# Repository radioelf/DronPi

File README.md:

# DronPi 
Placa sensores para [ardupilot](https://github.com/ArduPilot) y Raspberry o [DuePi](https://github.com/radioelf/Arduino-Due-mod-for-GPIO-compatible-Raspberry-Pi)

Sensores:  
    -***MS5611*** Sensor de presión barométrica (Bus SPI)   
    -***MPU9250*** 	Giroscopio/Acelerómetro/Compás interno/9-AXIS (Bus SPI)   
    -***MCP2515*** CAN Bus (Bus SPI)  
    -***ADS1115*** ADC 16bits (Bus I2C) dirección 0x48, canal 0 tensión, canal 1 intensidad  
    -***PCA9685*** Generador de PWM (Bus I2c) dirección 0x40 y 0x70(ALLCALL)

Periféricos: zumbador, RS-232, i2C, PowerOOF, PPM S-BUS, ADC, Can-Bus, HATs (Hardware Attached on Top)

http://radioelf.blogspot.com.es/  
https://www.youtube.com/watch?v=Fd6dcFx_-Ns (test..)

1/01/17
Changed IC12 SN74LVC1G07 by SN74AHC1G04 (to use S-bus)

## Creative Commons License Disclaimer

UNLESS OTHERWISE MUTUALLY AGREED TO BY THE PARTIES IN WRITING, LICENSOR OFFERS THE WORK AS-IS AND MAKES NO REPRESENTATIONS OR WARRANTIES OF ANY KIND CONCERNING THE WORK, EXPRESS, IMPLIED, STATUTORY OR OTHERWISE, INCLUDING, WITHOUT LIMITATION, WARRANTIES OF TITLE, MERCHANTIBILITY, FITNESS FOR A PARTICULAR PURPOSE, NONINFRINGEMENT, OR THE ABSENCE OF LATENT OR OTHER DEFECTS, ACCURACY, OR THE PRESENCE OF ABSENCE OF ERRORS, WHETHER OR NOT DISCOVERABLE. SOME JURISDICTIONS DO NOT ALLOW THE EXCLUSION OF IMPLIED WARRANTIES, SO SUCH EXCLUSION MAY NOT APPLY TO YOU. EXCEPT TO THE EXTENT REQUIRED BY APPLICABLE LAW, IN NO EVENT WILL LICENSOR BE LIABLE TO YOU ON ANY LEGAL THEORY FOR ANY SPECIAL, INCIDENTAL, CONSEQUENTIAL, PUNITIVE OR EXEMPLARY DAMAGES ARISING OUT OF THIS LICENSE OR THE USE OF THE WORK, EVEN IF LICENSOR HAS BEEN ADVISED OF THE POSSIBILITY OF SUCH DAMAGES.

http://creativecommons.org/licenses/by-sa/3.0/

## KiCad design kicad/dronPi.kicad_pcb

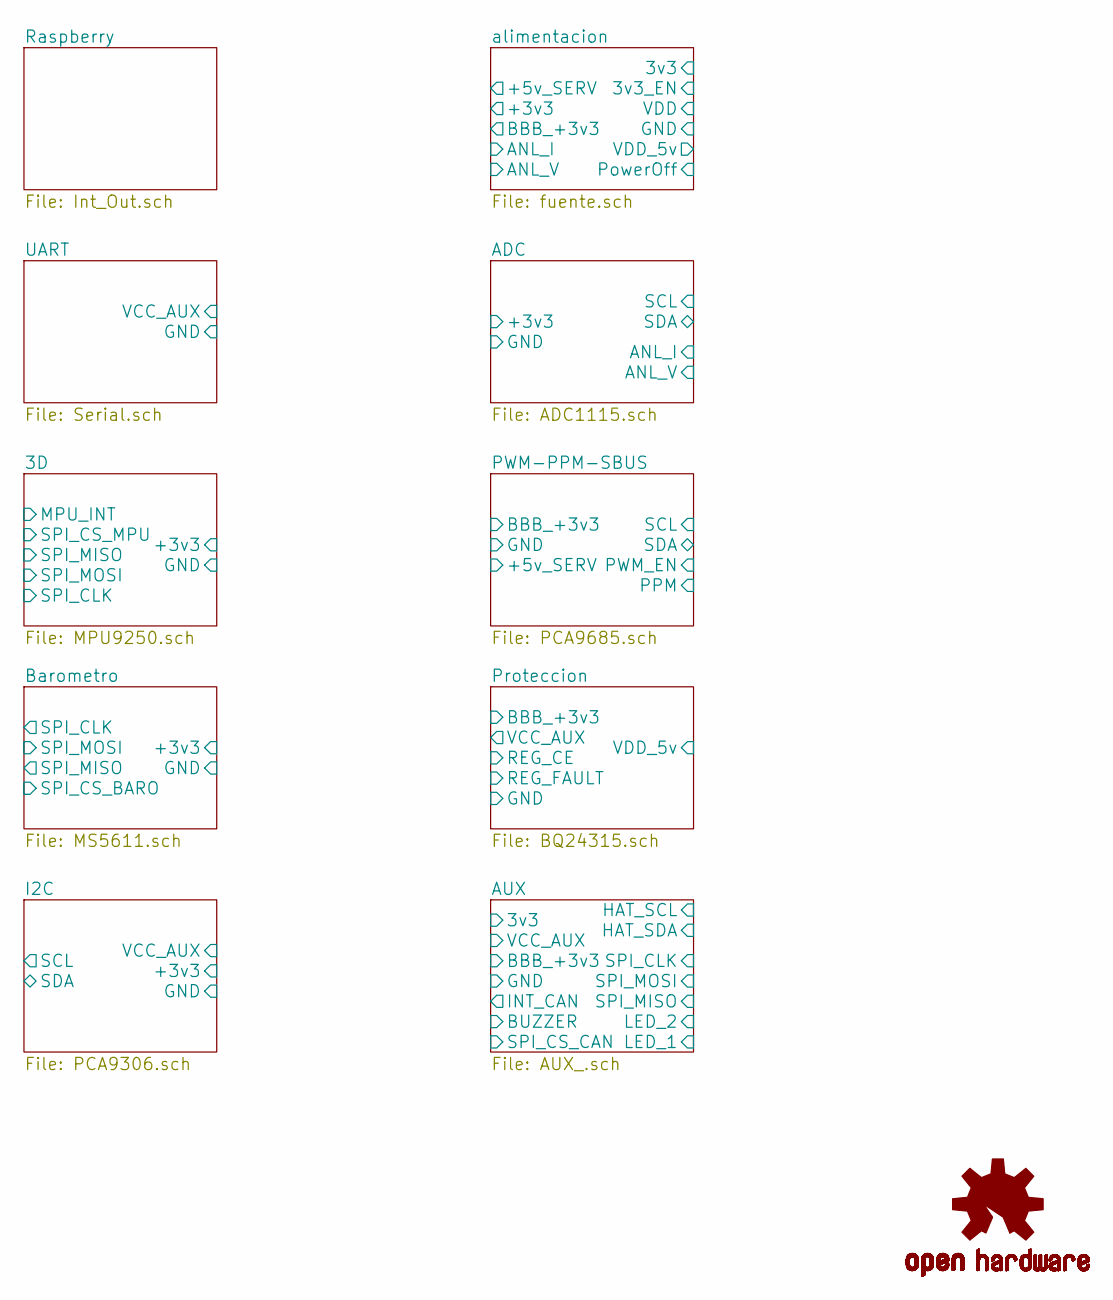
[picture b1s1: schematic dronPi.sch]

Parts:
M1: OSHW-LOGOS; OSHW-Logo2_7.3x6mm_SilkScreen

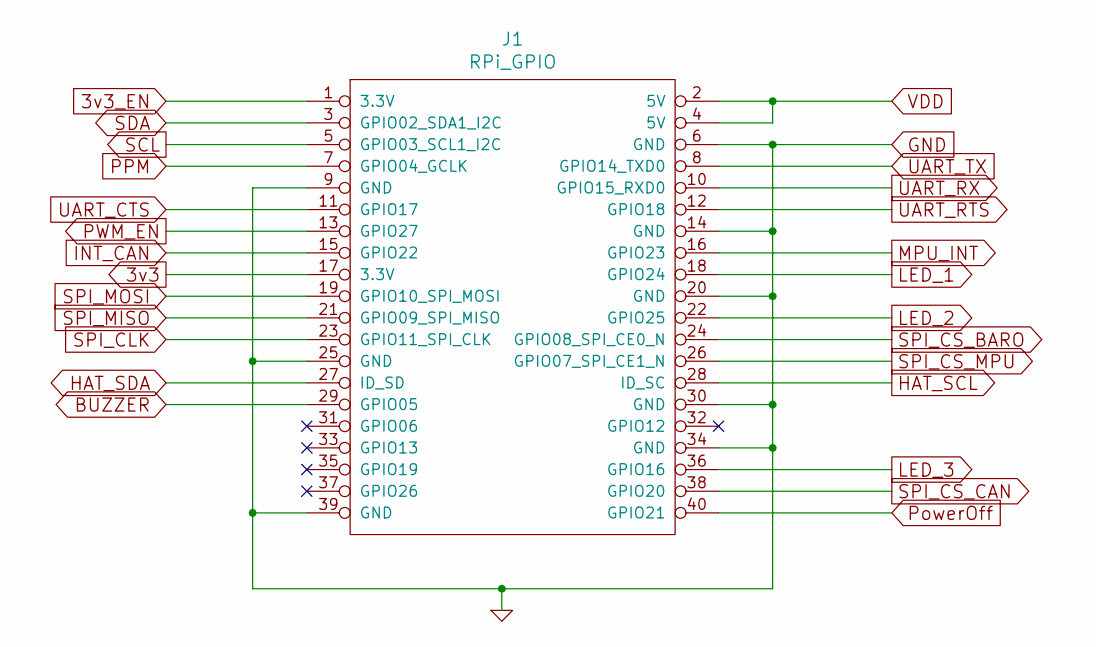
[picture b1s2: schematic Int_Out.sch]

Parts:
J1: RPi_GPIO; raspberrypi2

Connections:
3v3: J1.17 (3.3V); also elsewhere on the board
3v3_EN: J1.1 (3.3V); also elsewhere on the board
BUZZER: J1.29 (GPIO05); also elsewhere on the board
GND: J1.6 (GND), J1.9 (GND), J1.14 (GND), J1.20 (GND), J1.25 (GND), J1.30 (GND), J1.34 (GND), J1.39 (GND); also elsewhere on the board
HAT_SCL: J1.28 (ID_SC); also elsewhere on the board
HAT_SDA: J1.27 (ID_SD); also elsewhere on the board
INT_CAN: J1.15 (GPIO22); also elsewhere on the board
LED_1: J1.18 (GPIO24); also elsewhere on the board
LED_2: J1.22 (GPIO25); also elsewhere on the board
LED_3: J1.36 (GPIO16); also elsewhere on the board
MPU_INT: J1.16 (GPIO23); also elsewhere on the board
PPM: J1.7 (GPIO04_GCLK); also elsewhere on the board
PWM_EN: J1.13 (GPIO27); also elsewhere on the board
PowerOff: J1.40 (GPIO21); also elsewhere on the board
SCL: J1.5 (GPIO03_SCL1_I2C); also elsewhere on the board
SDA: J1.3 (GPIO02_SDA1_I2C); also elsewhere on the board
SPI_CLK: J1.23 (GPIO11_SPI_CLK); also elsewhere on the board
SPI_CS_BARO: J1.24 (GPIO08_SPI_CE0_N); also elsewhere on the board
SPI_CS_CAN: J1.38 (GPIO20); also elsewhere on the board
SPI_CS_MPU: J1.26 (GPIO07_SPI_CE1_N); also elsewhere on the board
SPI_MISO: J1.21 (GPIO09_SPI_MISO); also elsewhere on the board
SPI_MOSI: J1.19 (GPIO10_SPI_MOSI); also elsewhere on the board
UART_CTS: J1.11 (GPIO17); also elsewhere on the board
UART_RTS: J1.12 (GPIO18); also elsewhere on the board
UART_RX: J1.10 (GPIO15_RXD0); also elsewhere on the board
UART_TX: J1.8 (GPIO14_TXD0); also elsewhere on the board
VDD: J1.2 (5V), J1.4 (5V); also elsewhere on the board

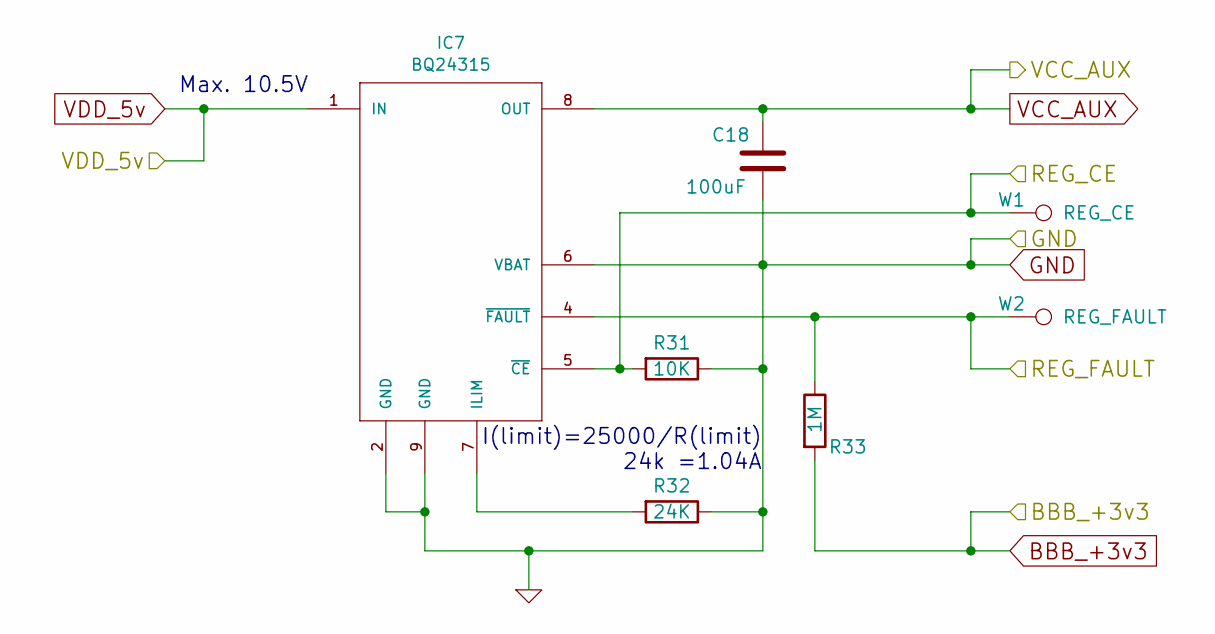
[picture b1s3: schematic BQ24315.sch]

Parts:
C18: 100uF; C_1210
IC7: BQ24315; BQ24313_DSG_8
R31: 10K; R_0805
R32: 24K; R_0805
R33: 1M; R_0805
W1: REG_CE; Measurement_Point_Round-SMD-Pad_Small
W2: REG_FAULT; Measurement_Point_Round-SMD-Pad_Small

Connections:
/Proteccion/REG_CE: IC7.5 (~CE), R31.2, W1.1
/Proteccion/REG_FAULT: IC7.4 (~FAULT), R33.1, W2.1
BBB_+3v3: R33.2; also elsewhere on the board
GND: C18.2, IC7.2 (GND), IC7.6 (VBAT), IC7.9 (GND), R31.1, R32.1; also elsewhere on the board
unnamed: IC7.7 (ILIM), R32.2
VCC_AUX: C18.1, IC7.8 (OUT); also elsewhere on the board
VDD_5v: IC7.1 (IN); also elsewhere on the board

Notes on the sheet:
I(limit)=25000/R(limit) 24k =1.04A
Max. 10.5V

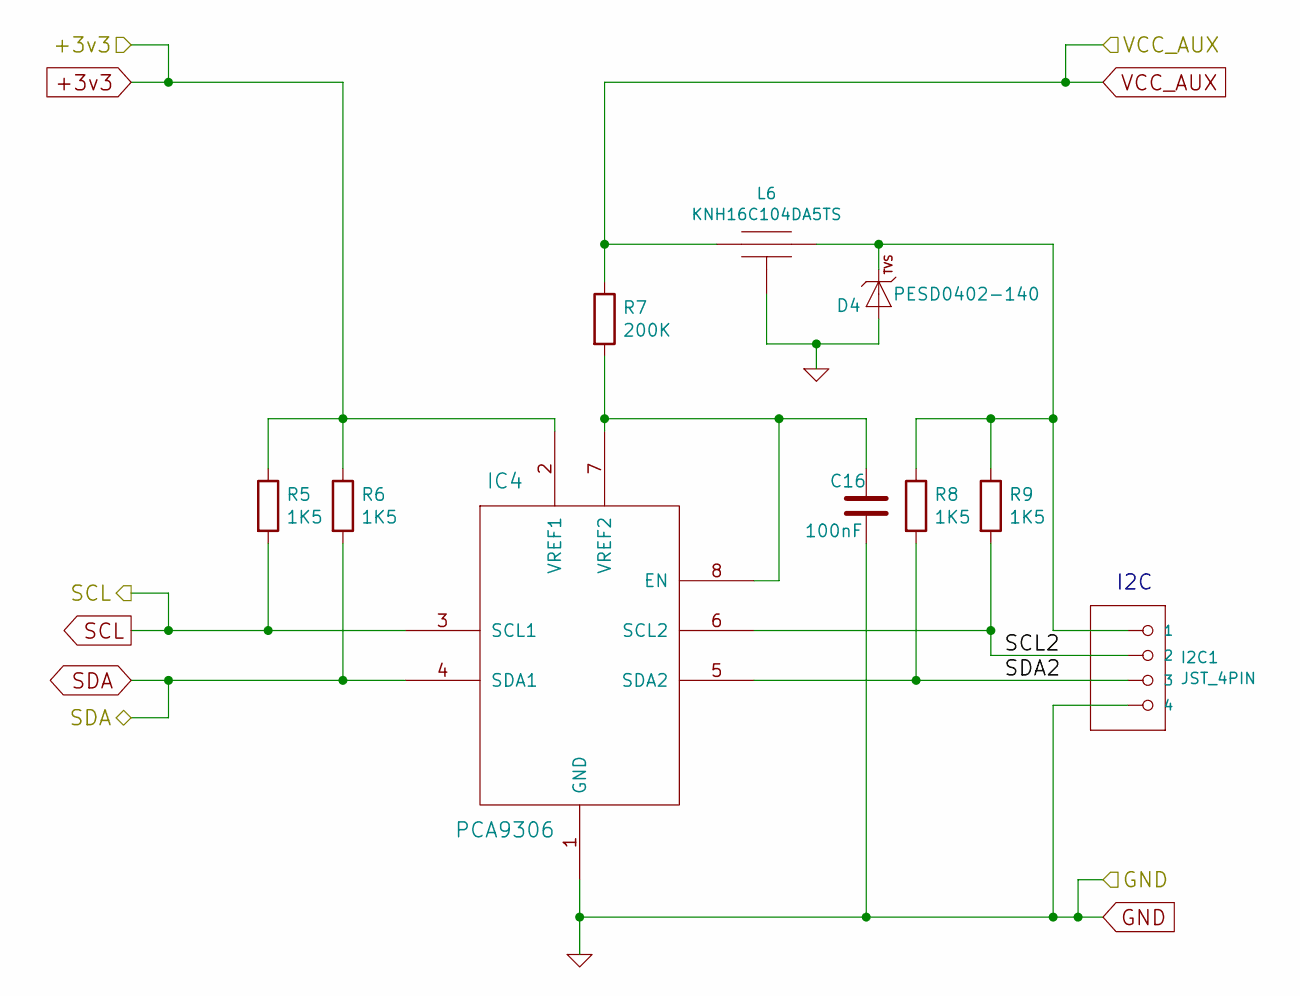
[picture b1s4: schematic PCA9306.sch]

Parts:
C16: 100nF; C_0805
D4: PESD0402-140; C_0402
I2C1: JST_4PIN; JST_EH_B04B-EH-A_04x2.50mm_Straight
IC4: PCA9306; MSOP-8_3x3mm_Pitch0.65mm
L6: KNH16C104DA5TS; KYOCERA-KNH16-DA
R5, R6, R8, R9: 1K5; R_0805
R7: 200K; R_0805

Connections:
+3v3: IC4.2 (VREF1), R5.1, R6.1; also elsewhere on the board
/I2C/SCL2: I2C1.2, IC4.6 (SCL2), R9.2
/I2C/SDA2: I2C1.3, IC4.5 (SDA2), R8.2
GND: C16.2, D4.2 (A), I2C1.4, IC4.1 (GND), L6.P$3, L6.P$4, L6.P$5; also elsewhere on the board
unnamed: C16.1, IC4.7 (VREF2), IC4.8 (EN), R7.2
unnamed: D4.1 (C), I2C1.1, L6.P$2, R8.1, R9.1
SCL: IC4.3 (SCL1), R5.2; also elsewhere on the board
SDA: IC4.4 (SDA1), R6.2; also elsewhere on the board
VCC_AUX: L6.P$1, R7.1; also elsewhere on the board

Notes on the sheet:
I2C

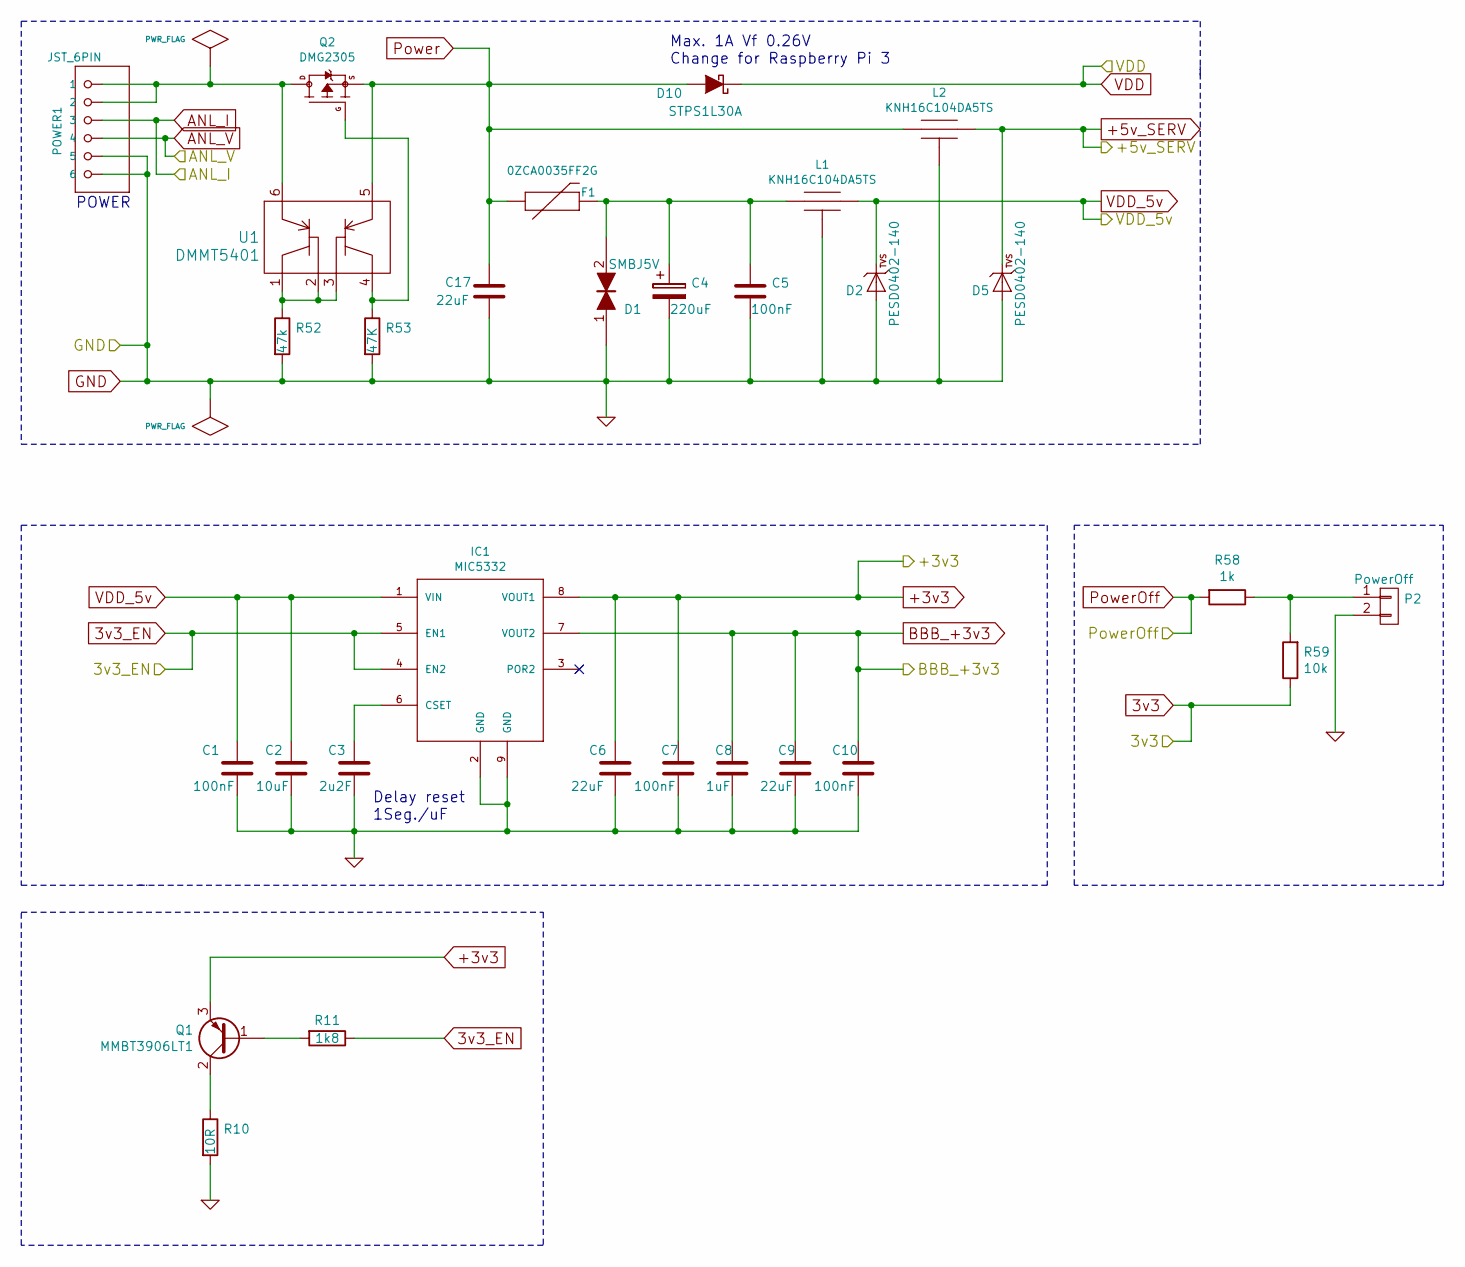
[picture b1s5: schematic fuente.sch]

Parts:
C1, C5, C7, C10: 100nF; C_0805
C2: 10uF; C_0805
C3: 2u2F; C_0805
C4: 220uF; TantalC_SizeD_EIA-7343_Reflow
C6, C9, C17: 22uF; C_0805
C8: 1uF; C_0805
D1: SMBJ5V; DO-214AA
D2, D5: PESD0402-140; C_0402
D10: STPS1L30A; SMA_Standard
F1: 0ZCA0035FF2G; Fuse_SMD1206_Wave
IC1: MIC5332; MLF-8-1EP
L1, L2: KNH16C104DA5TS; KYOCERA-KNH16-DA
P2: PowerOff; JST_EH_B02B-EH-A_02x2.50mm_Straight
POWER1: JST_6PIN; JST_EH_B06B-EH-A_06x2.50mm_Straight
Q1: MMBT3906LT1; SOT-23
Q2: DMG2305; SOT23-3
R10: 10R; R_0805
R11: 1k8; R_0805
R52: 47k; R_0805
R53: 47K; R_0805
R58: 1k; R_0805
R59: 10k; R_0805
U1: DMMT5401; SOT-23-6

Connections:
3v3: R59.1; also elsewhere on the board
3v3_EN: IC1.4 (EN2), IC1.5 (EN1), R11.1; also elsewhere on the board
+3v3: C6.1, C7.1, IC1.8 (VOUT1), Q1.3 (E); also elsewhere on the board
+5v_SERV: D5.1 (C), L2.P$2; also elsewhere on the board
ANL_I: POWER1.3; also elsewhere on the board
ANL_V: POWER1.4; also elsewhere on the board
BBB_+3v3: C8.1, C9.1, C10.1, IC1.7 (VOUT2); also elsewhere on the board
GND: C1.2, C2.2, C3.2, C4.2, C5.2, C6.2, C7.2, C8.2, C9.2, C10.2, C17.2, D1.1, D2.2 (A), D5.2 (A), IC1.2 (GND), IC1.9 (GND), L1.P$3, L1.P$4, L1.P$5, L2.P$3, L2.P$4, L2.P$5, P2.2, POWER1.5, POWER1.6, R10.2, R52.2, R53.2; also elsewhere on the board
unnamed: C3.1, IC1.6 (CSET)
unnamed: C4.1, C5.1, D1.2, F1.2, L1.P$1
unnamed: P2.1, R58.1, R59.2
unnamed: POWER1.1, POWER1.2, Q2.3 (D), U1.6
unnamed: Q1.1 (B), R11.2
unnamed: Q1.2 (C), R10.1
unnamed: Q2.1 (G), R53.1, U1.4
unnamed: R52.1, U1.1, U1.2, U1.3
Power: C17.1, D10.2 (A), F1.1, L2.P$1, Q2.2 (S), U1.5
PowerOff: R58.2; also elsewhere on the board
VDD: D10.1 (K); also elsewhere on the board
VDD_5v: C1.1, C2.1, D2.1 (C), IC1.1 (VIN), L1.P$2; also elsewhere on the board

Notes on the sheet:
Delay reset 1Seg./uF
POWER
Max. 1A Vf 0.26V Change for Raspberry Pi 3

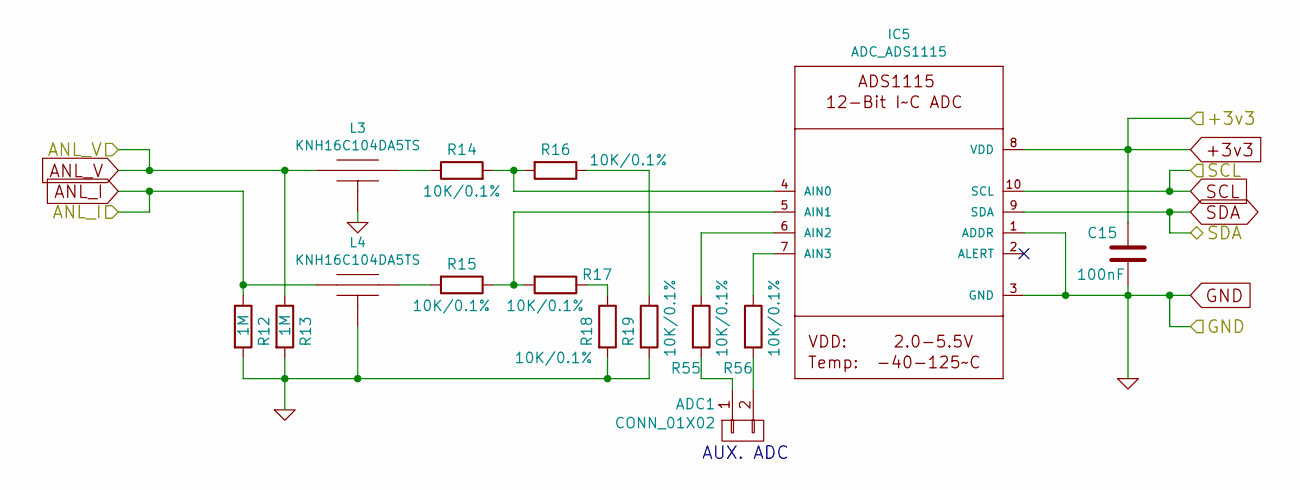
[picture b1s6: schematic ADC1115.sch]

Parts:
ADC1: CONN_01X02; JST_EH_B02B-EH-A_02x2.50mm_Straight
C15: 100nF; C_0805
IC5: ADC_ADS1115; MSOP-10_3x3mm_Pitch0.5mm
L3, L4: KNH16C104DA5TS; KYOCERA-KNH16-DA
R12, R13: 1M; R_0805
R14, R15, R16, R17, R18, R19, R55, R56: 10K/0.1%; R_0805

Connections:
+3v3: C15.1, IC5.8 (VDD); also elsewhere on the board
ANL_I: L4.P$1, R12.1; also elsewhere on the board
ANL_V: L3.P$1, R13.1; also elsewhere on the board
GND: C15.2, IC5.1 (ADDR), IC5.3 (GND), L3.P$3, L3.P$4, L3.P$5, L4.P$3, L4.P$4, L4.P$5, R12.2, R13.2, R18.2, R19.2; also elsewhere on the board
unnamed: ADC1.1, R55.2
unnamed: ADC1.2, R56.2
unnamed: IC5.4 (AIN0), R14.2, R16.2
unnamed: IC5.5 (AIN1), R15.1, R17.2
unnamed: IC5.6 (AIN2), R55.1
unnamed: IC5.7 (AIN3), R56.1
unnamed: L3.P$2, R14.1
unnamed: L4.P$2, R15.2
unnamed: R16.1, R19.1
unnamed: R17.1, R18.1
SCL: IC5.10 (SCL); also elsewhere on the board
SDA: IC5.9 (SDA); also elsewhere on the board

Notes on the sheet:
AUX. ADC

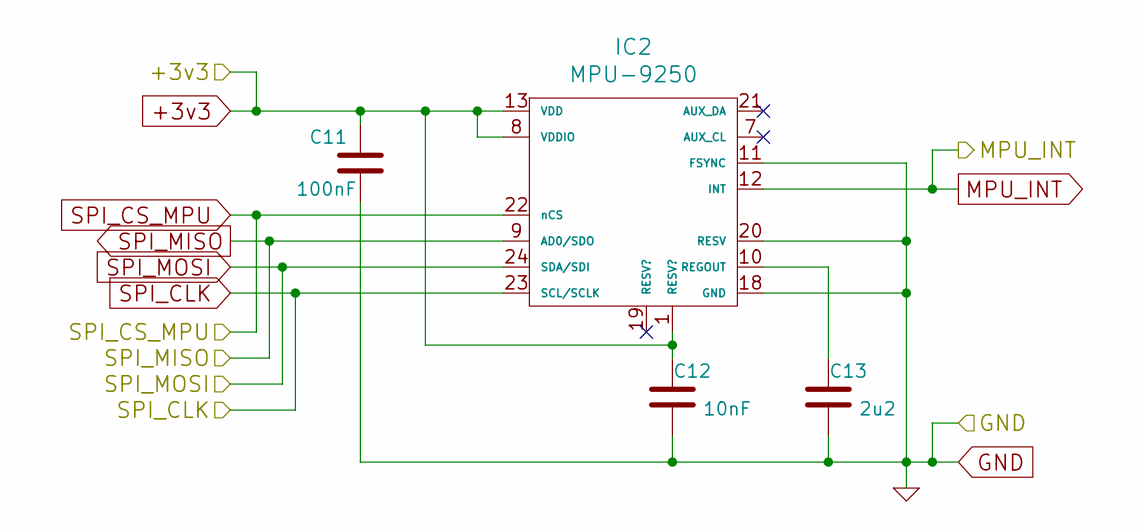
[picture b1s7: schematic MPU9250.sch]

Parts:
C11: 100nF; C_0805
C12: 10nF; C_0805
C13: 2u2; C_0805
IC2: MPU-9250; QFN-24-1EP_3x3mm_Pitch0.4mm

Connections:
+3v3: C11.1, C12.1, IC2.1 (RESV?), IC2.8 (VDDIO), IC2.13 (VDD); also elsewhere on the board
GND: C11.2, C12.2, C13.2, IC2.11 (FSYNC), IC2.18 (GND), IC2.20 (RESV); also elsewhere on the board
MPU_INT: IC2.12 (INT); also elsewhere on the board
unnamed: C13.1, IC2.10 (REGOUT)
SPI_CLK: IC2.23 (SCL/SCLK); also elsewhere on the board
SPI_CS_MPU: IC2.22 (nCS); also elsewhere on the board
SPI_MISO: IC2.9 (AD0/SDO); also elsewhere on the board
SPI_MOSI: IC2.24 (SDA/SDI); also elsewhere on the board

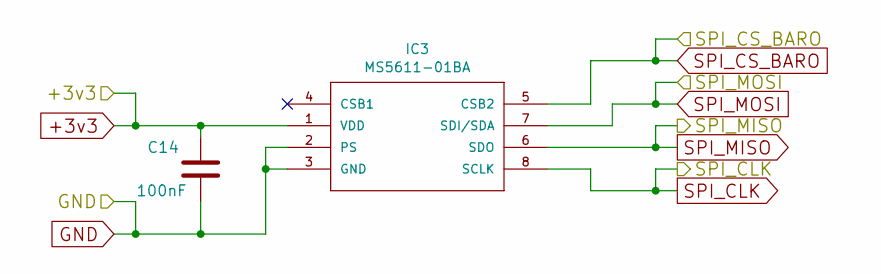
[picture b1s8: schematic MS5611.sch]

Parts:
C14: 100nF; C_0805
IC3: MS5611-01BA; MS5611

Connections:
+3v3: C14.1, IC3.1 (VDD); also elsewhere on the board
GND: C14.2, IC3.2 (PS), IC3.3 (GND); also elsewhere on the board
SPI_CLK: IC3.8 (SCLK); also elsewhere on the board
SPI_CS_BARO: IC3.5 (CSB2); also elsewhere on the board
SPI_MISO: IC3.6 (SDO); also elsewhere on the board
SPI_MOSI: IC3.7 (SDI/SDA); also elsewhere on the board

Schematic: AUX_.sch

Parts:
BUZZER1: CONN_01X04; JST_EH_B02B-EH-A_02x2.50mm_Straight
C20, C22: 22pF; C_0805
C21, C23, C24: 100nF; C_0805
CAN-Bus1: JST_4PIN; JST_EH_B04B-EH-A_04x2.50mm_Straight
D6: LED_rojo; LED_0603
D7: LED_verde; LED_0603
D8: LED_azul; LED_0603
D9: PESD0402-140; C_0402
D11: verde; LED_0603
D12: Rojo; LED_0603
D14: LED_naranja; LED_0603
IC8: MCP2515; SOIC-18
IC9: MCP2551; SOIC-8-N
IC10: 24AA32; MSOP-8_3x3mm_Pitch0.65mm
JP1: JUMPER; GS2
JP2: JUMPER3; GS3
L7: KNH16C104DA5TS; KYOCERA-KNH16-DA
Q3: MMBT3906; SOT-23
R34, R35, R60: 680; R_0805
R36: 820; R_0805
R44: 18K; R_0805
R45, R46: 560; R_0805
R47: 10K; R_0805
R48, R54, R61: 1K; R_0805
R49: 120R; R_0805
R50: 3K9; R_0805
R51: 3k9; R_0805
R57: 10k; R_0805
XT2: 16Mhz; HC-18UV

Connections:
3v3: C24.2, IC10.8 (VCC), JP2.1, R50.1, R51.1; also elsewhere on the board
BBB_+3v3: C21.2, IC8.18 (Vdd), R45.1, R46.1, R47.2; also elsewhere on the board
BUZZER: R61.2; also elsewhere on the board
GND: BUZZER1.2, C20.2, C21.1, C22.2, C23.2, C24.1, CAN-Bus1.4, D9.2 (A), IC8.9 (Vss), IC9.2 (Vss), IC10.1 (A0), IC10.2 (A1), IC10.3 (A2), IC10.4 (GND), JP2.3, L7.P$3, L7.P$4, L7.P$5, R34.2, R44.1, R48.2; also elsewhere on the board
HAT_SCL: IC10.6 (SCL), R50.2; also elsewhere on the board
HAT_SDA: IC10.5 (SDA), R51.2; also elsewhere on the board
INT_CAN: IC8.12 (~INT); also elsewhere on the board
LED_1: R35.2; also elsewhere on the board
LED_2: R36.2; also elsewhere on the board
LED_3: R60.2; also elsewhere on the board
unnamed: BUZZER1.1, Q3.1 (B), Q3.3 (C), R61.1
unnamed: C20.1, IC8.8 (OSC1), XT2.1
unnamed: C22.1, IC8.7 (OSC2), XT2.2
unnamed: C23.1, CAN-Bus1.1, D9.1 (C), IC9.3 (Vdd), L7.P$2
unnamed: CAN-Bus1.2, IC9.7 (CANH), R49.2
unnamed: CAN-Bus1.3, IC9.6 (CANL), JP1.2
unnamed: D6.1 (K), R34.1
unnamed: D7.1 (K), R35.1
unnamed: D8.1 (K), R36.1
unnamed: D11.1 (K), IC8.11 (~RX0BF)
unnamed: D11.2 (A), R45.2
unnamed: D12.1 (K), IC8.10 (~RX1BF)
unnamed: D12.2 (A), R46.2
unnamed: D14.1 (K), R60.1
unnamed: IC8.1 (TXCAN), IC9.1 (TXD)
unnamed: IC8.2 (RXCAN), R44.2, R57.2
unnamed: IC8.17 (~RESET), R47.1
unnamed: IC9.4 (RXD), R57.1
unnamed: IC9.8 (Rs), R48.1
unnamed: IC10.7 (WP), R54.2
unnamed: JP1.1, R49.1
unnamed: JP2.2, R54.1
SPI_CLK: IC8.13 (SCK); also elsewhere on the board
SPI_CS_CAN: IC8.16 (~CS); also elsewhere on the board
SPI_MISO: IC8.15 (SO); also elsewhere on the board
SPI_MOSI: IC8.14 (SI); also elsewhere on the board
VCC_AUX: D6.2 (A), D7.2 (A), D8.2 (A), D14.2 (A), L7.P$1, Q3.2 (E); also elsewhere on the board

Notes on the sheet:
CAN Bus
AUX. Buzzer

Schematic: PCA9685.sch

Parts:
C19, C25: 100nF; C_0805
D13: PESD0402-140; C_0402
F2: 0ZCA0035FF2G; Fuse_SMD1206_Wave
IC6: PCA9685; TSSOP-28_4.4x9.7mm_Pitch0.65mm
IC11: MAX3370; SC70-5
IC12: SN74LVC1G07; SC70-5
JP3: JUMPER3; GS3
P1: CONN_3X16; IDC_Header_Straight_48pins
R20, R21: 10K; R_0805
R22, R23, R24, R25, R26, R27, R28, R29, R37, R38, R39, R40, R41, R42, R43: 220; R_0805
R30: 100; R_0805
XT1: CRYSTAL_ASE-25mhz; ASEseries

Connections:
+5v_SERV: C25.2, F2.2, IC11.5 (VCC), IC12.5 (VCC); also elsewhere on the board
/PWM-PPM-SBUS/PPM_: D13.1 (C), IC12.2 (I), JP3.1, R30.2
/PWM-PPM-SBUS/SBUS_: IC12.4 (O), JP3.3
BBB_+3v3: C19.1, IC6.28 (Vdd), IC11.1 (VL), R20.1, XT1.4 (VDD); also elsewhere on the board
GND: C19.2, C25.1, D13.2 (A), IC6.14 (Vss), IC11.2 (GND), IC12.3 (GND), P1.3 (p3), P1.6, P1.9, P1.12, P1.15, P1.18, P1.21, P1.24, P1.27, P1.30, P1.33, P1.36, P1.39, P1.42, P1.45, P1.48, R21.2, XT1.2 (VSS); also elsewhere on the board
unnamed: F2.1, P1.2, P1.5, P1.8, P1.11, P1.14, P1.17, P1.20, P1.23, P1.26, P1.29, P1.32, P1.35, P1.38, P1.41, P1.44, P1.47 (P44)
unnamed: IC6.1 (A0), IC6.2 (A1), IC6.3 (A2), IC6.4 (A3), IC6.5 (A4), IC6.24 (A5), R21.1
unnamed: IC6.6 (LED0), R37.2
unnamed: IC6.7 (LED1), R38.2
unnamed: IC6.8 (LED2), R39.2
unnamed: IC6.9 (LED3), R22.2
unnamed: IC6.10 (LED4), R23.2
unnamed: IC6.11 (LED5), R24.2
unnamed: IC6.12 (LED6), R25.2
unnamed: IC6.13 (LED7), R26.2
unnamed: IC6.15 (LED8), R27.2
unnamed: IC6.16 (LED9), R28.2
unnamed: IC6.17 (LED10), R29.2
unnamed: IC6.18 (LED11), R40.2
unnamed: IC6.19 (LED12), R41.2
unnamed: IC6.20 (LED13), R42.2
unnamed: IC6.21 (LED14), R43.2
unnamed: IC6.25 (EXTCLK), XT1.3 (OUT)
unnamed: IC11.4 (I/O_VCC), JP3.2
unnamed: P1.1, R37.1
unnamed: P1.4, R38.1
unnamed: P1.7, R39.1
unnamed: P1.10, R22.1
unnamed: P1.13, R23.1
unnamed: P1.16, R24.1
unnamed: P1.19 (P29), R25.1
unnamed: P1.22, R26.1
unnamed: P1.25, R27.1
unnamed: P1.28, R28.1
unnamed: P1.31, R29.1
unnamed: P1.34, R40.1
unnamed: P1.37, R41.1
unnamed: P1.40, R42.1
unnamed: P1.43, R43.1
unnamed: P1.46, R30.1
PPM: IC11.3 (I/O_VL); also elsewhere on the board
PWM_EN: IC6.23 (~OE), R20.2; also elsewhere on the board
SCL: IC6.26 (SCL); also elsewhere on the board
SDA: IC6.27 (SDA); also elsewhere on the board

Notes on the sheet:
YSO321SR

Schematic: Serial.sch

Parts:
D3: PESD0402-140; C_0402
L5: KNH16C104DA5TS; KYOCERA-KNH16-DA
R1, R2, R3, R4: 120R; R_0805
USART5: JST_6PIN; JST_EH_B06B-EH-A_06x2.50mm_Straight

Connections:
GND: D3.2 (A), L5.P$3, L5.P$4, L5.P$5, USART5.6; also elsewhere on the board
unnamed: D3.1 (C), L5.P$1, USART5.1
unnamed: R1.2, USART5.5
unnamed: R2.2, USART5.4
unnamed: R3.2, USART5.3
unnamed: R4.2, USART5.2
UART_CTS: R2.1; also elsewhere on the board
UART_RTS: R1.1; also elsewhere on the board
UART_RX: R3.1; also elsewhere on the board
UART_TX: R4.1; also elsewhere on the board
VCC_AUX: L5.P$2; also elsewhere on the board

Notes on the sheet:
GPS USART

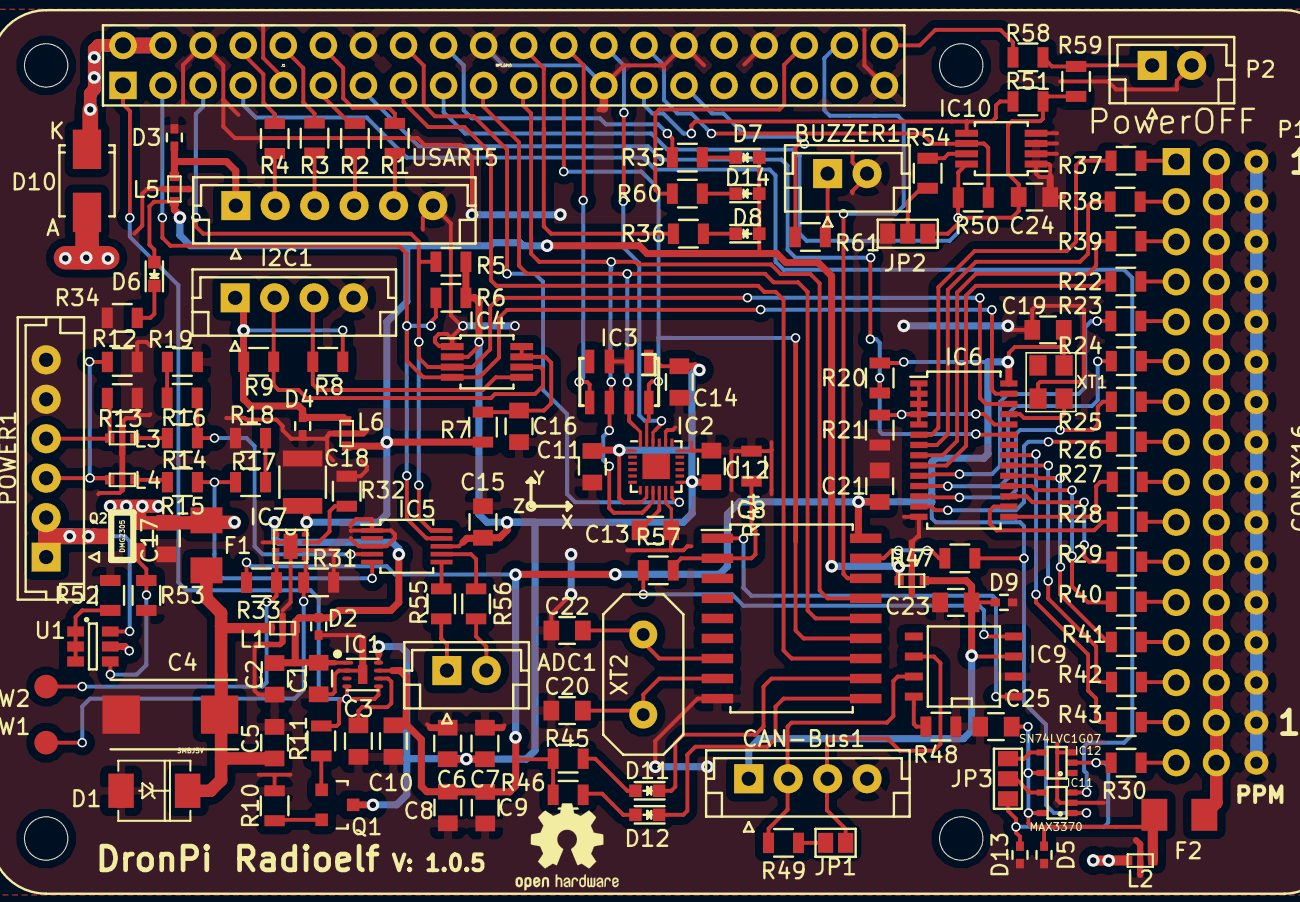
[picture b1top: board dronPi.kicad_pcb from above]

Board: 2 copper layers, 141 parts (0 on the bottom side), 125 nets.

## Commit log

2016-10-01 3D pcb DronPi v1.0.4
    Vista de la placa DronPi en 3D con Kicad
2016-10-02 Create imges
2016-10-02 Create imagenes
2016-10-02 Imagen de la placa en 3d según Kicad
2016-10-02 Create Ficheros PCB
2016-10-02 Create Ficheros gerber
2016-10-02 Update Ficheros PCB
2016-10-02 GPIO Raspberry for DronPi
2016-10-03 Imágen de la placa (1.0.2)
2016-10-03 Esquemas en pdf
2016-10-14 V1.0.5
    Pequeños cambios
2016-10-14 PCB v1.0.5
2016-10-14 V1.0.5
2016-11-14 Create buzzer
2016-11-22 PCB 1.0.5
2017-01-25 PCB v1.0.5 Mounted
2017-02-13 Library DronPi

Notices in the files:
parts and their libraries:
Copyright 2016 Accelerated Designs. All rights reserved.
